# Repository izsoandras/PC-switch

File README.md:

# PC-switch
Simple gadget to turn on my PC remotely. I could have used my motherboards Wake on LAN service, but it is disabled on my student hostel's network.

A webserver is running on the ESP8266 with a very simple REST API. After authentication the client side offers a few buttons. These buttons send http requests to the proper URI address, and the ESP performs the required action.
The available options:
- **Turn on:** imitates the pressing of the power button for 500ms 
- **Reset:** imitates the pressing of the reset button for 500ms
- **Refresh:** asks the server for the current state of the PC (does not work at this time)
- **Kill:** shuts down the PC. The same as turn on but for 4s

The webpage also displays the current state of the PC.

The circuit is fairly simple. You can plug the board on the place of the front panel header of the mother board. Since I used long pin headers, the wires running to the chassis's front panel can be plugged in aswell
I used two FETs paralell to the power and reset button, to imitate the press of those buttons. There are also LEDs on the same pins as the FETs' gates for debug purposes.
The PC's state could be read from the Power and HDD LEDs' state.

The current problem is that, I did not measure the LEDs' active state, just assumed it's high active. Unfortunately my motherboard is more complicated than that.
If the PC os off, the + pin of the LED is on 5V, and the - pin is on 3V. If it's turned on the pins are on 3V and 0.1V respectively.

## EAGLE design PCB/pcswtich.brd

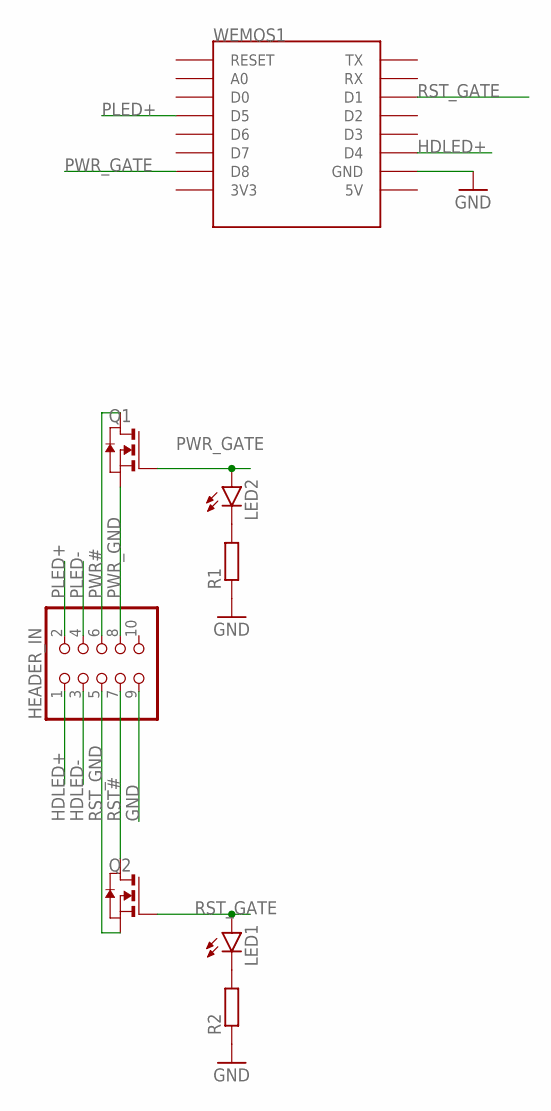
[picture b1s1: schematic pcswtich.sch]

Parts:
HEADER_IN: PINHD-2X5; 2X05
LED1, LED2: LEDCHIPLED_0805; CHIPLED_0805
Q1, Q2: NMOSSOT23; SOT-23
R1, R2: R-EU_R0805; R0805
WEMOS1: WEMOS-D1-MINI

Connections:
GND: HEADER_IN.9, R1.1, R2.1, WEMOS1.GND
HDLED+: HEADER_IN.1, WEMOS1.D4
HDLED-: HEADER_IN.3
unnamed: LED2.C, R1.2
unnamed: LED1.C, R2.2
PLED+: HEADER_IN.2, WEMOS1.D5
PLED-: HEADER_IN.4
PWR#: HEADER_IN.6, Q1.1 (D)
PWR_GATE: LED2.A, Q1.3 (G), WEMOS1.D8
PWR_GND: HEADER_IN.8, Q1.2 (S)
RST#: HEADER_IN.7, Q2.1 (D)
RST_GATE: LED1.A, Q2.3 (G), WEMOS1.D1
RST_GND: HEADER_IN.5, Q2.2 (S)

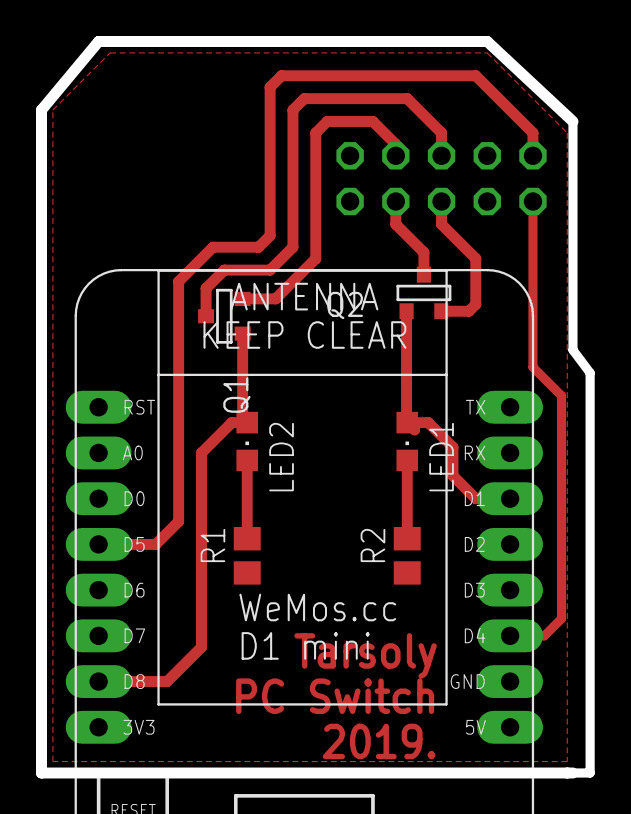
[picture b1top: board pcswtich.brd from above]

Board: 2 copper layers, 30.5 x 40.6 mm, 8 parts (1 on the bottom side), 11 nets.

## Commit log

2019-08-22 Initialize commit
2019-08-22 added README.md
2019-08-22 Added kill command
2019-08-22 Updated README.md with kill
2025-01-14 Modify code so that secrets are safe
